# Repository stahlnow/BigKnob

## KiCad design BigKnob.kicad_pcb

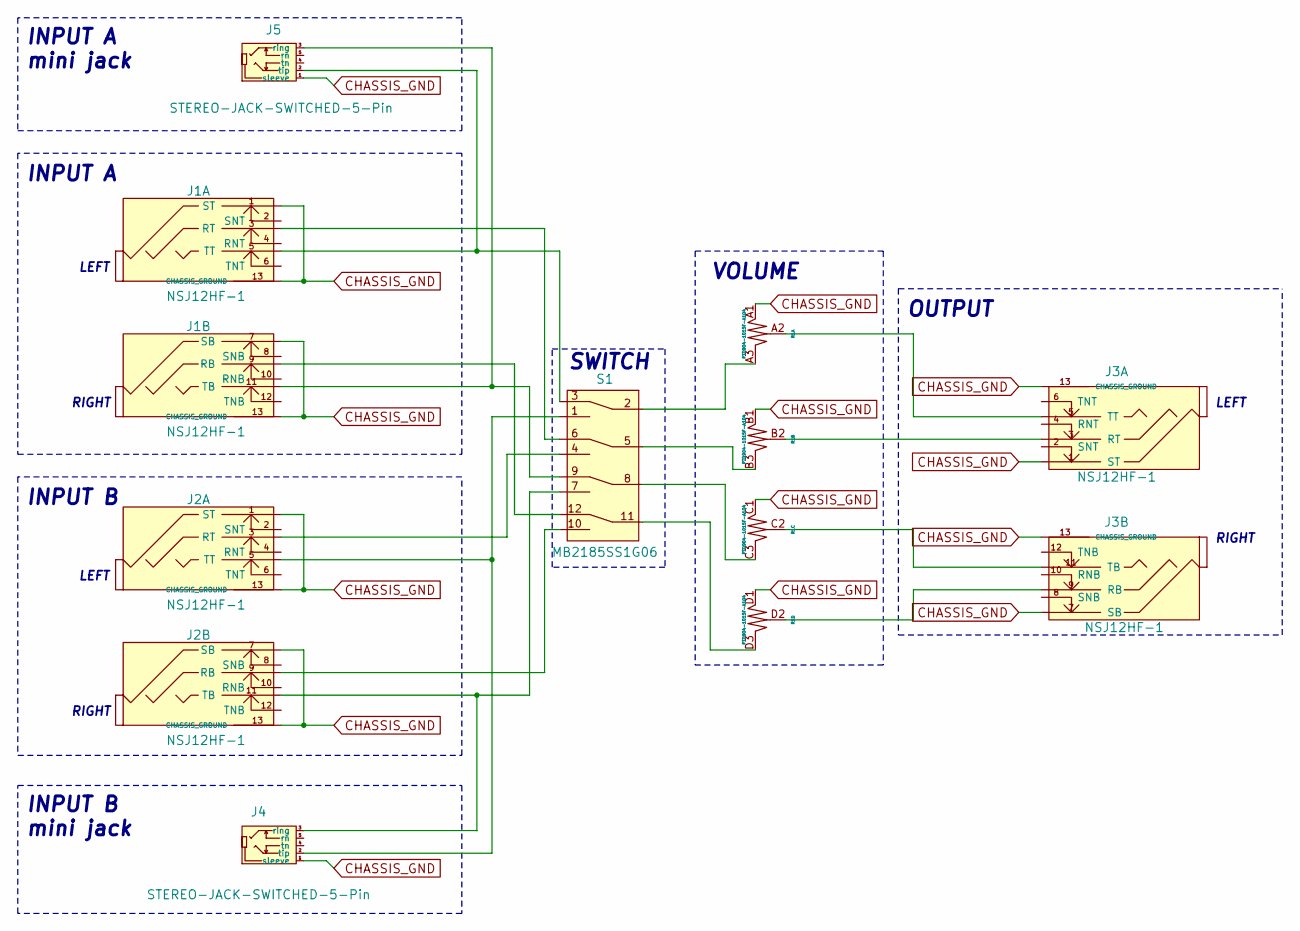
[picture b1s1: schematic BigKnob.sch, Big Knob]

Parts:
J1, J2, J3: NSJ12HF-1
J4, J5: STEREO-JACK-SWITCHED-5-Pin; Stereo-Mini-Jack-Switched-TRS-5-Pin
R1: PTD904-1015F-A104
S1: MB2185SS1G06

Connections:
CHASSIS_GND: J1.1 (ST), J1.7 (SB), J1.13 (CHASSIS_GROUND), J2.1 (ST), J2.7 (SB), J2.13 (CHASSIS_GROUND), J3.1 (ST), J3.7 (SB), J3.13 (CHASSIS_GROUND), J4.1 (sleeve), J5.1 (sleeve), R1.A1, R1.B1, R1.C1, R1.D1
unnamed: J1.3 (RT), S1.6
unnamed: J1.5 (TT), J5.2 (tip), S1.3
unnamed: J1.9 (RB), S1.12
unnamed: J1.11 (TB), J5.3 (ring), S1.9
unnamed: J2.3 (RT), S1.4
unnamed: J2.5 (TT), J4.2 (tip), S1.1
unnamed: J2.9 (RB), S1.10
unnamed: J2.11 (TB), J4.3 (ring), S1.7
unnamed: J3.3 (RT), R1.B2
unnamed: J3.5 (TT), R1.A2
unnamed: J3.9 (RB), R1.D2
unnamed: J3.11 (TB), R1.C2
unnamed: R1.A3, S1.2
unnamed: R1.B3, S1.5
unnamed: R1.C3, S1.8
unnamed: R1.D3, S1.11

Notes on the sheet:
INPUT A
INPUT B
LEFT
RIGHT
OUTPUT
INPUT B mini jack
INPUT A mini jack
SWITCH
VOLUME

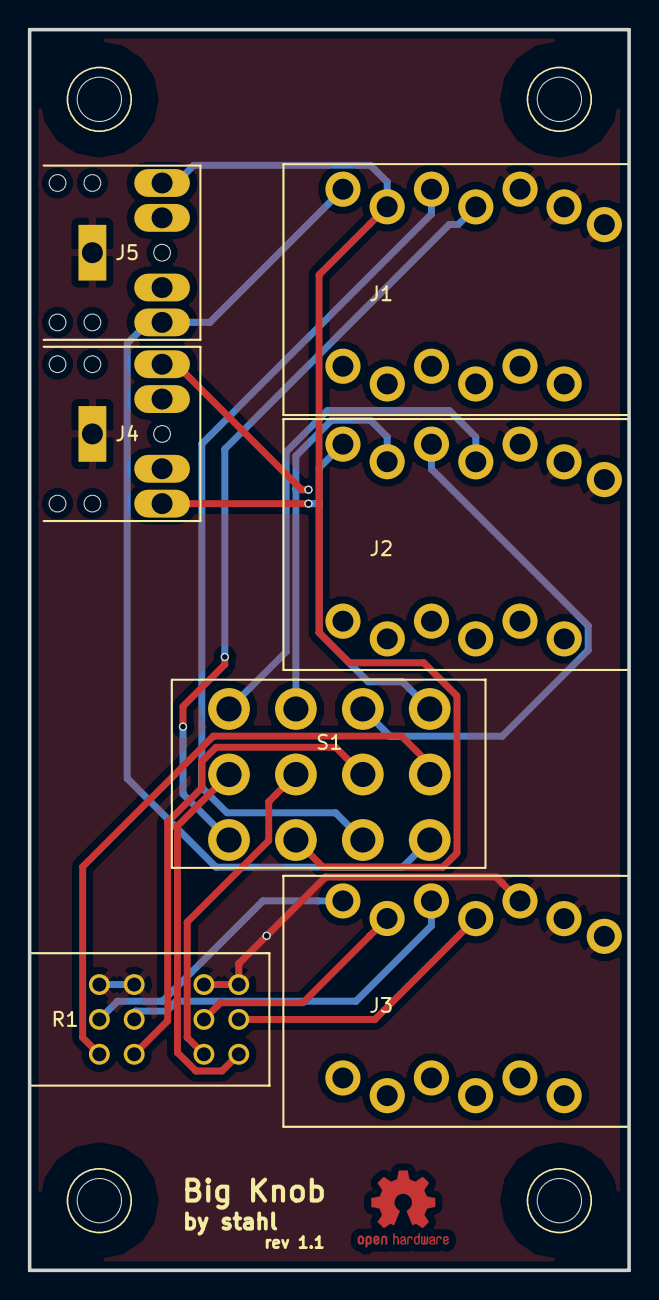
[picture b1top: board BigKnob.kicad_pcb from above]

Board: 2 copper layers, 43.0 x 89.0 mm, 7 parts (0 on the bottom side), 17 nets.

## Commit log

2017-05-14 :baby:
2017-05-15 add oshw logo :cake:
2017-05-15 add zip :rocket:
2017-05-16 update library, doc
2017-05-16 README :whale:
2017-06-08 :punch: fixed schema
2017-06-08 case
2017-06-08 update gerber
2017-06-08 update 3d / case
2017-06-08 :rocket: zipped
2017-07-25 fix library paths
2017-07-25 :punch: v1.1
2017-07-26 :rocket: update pic
2017-07-26 v1.1
2018-01-13 update case
